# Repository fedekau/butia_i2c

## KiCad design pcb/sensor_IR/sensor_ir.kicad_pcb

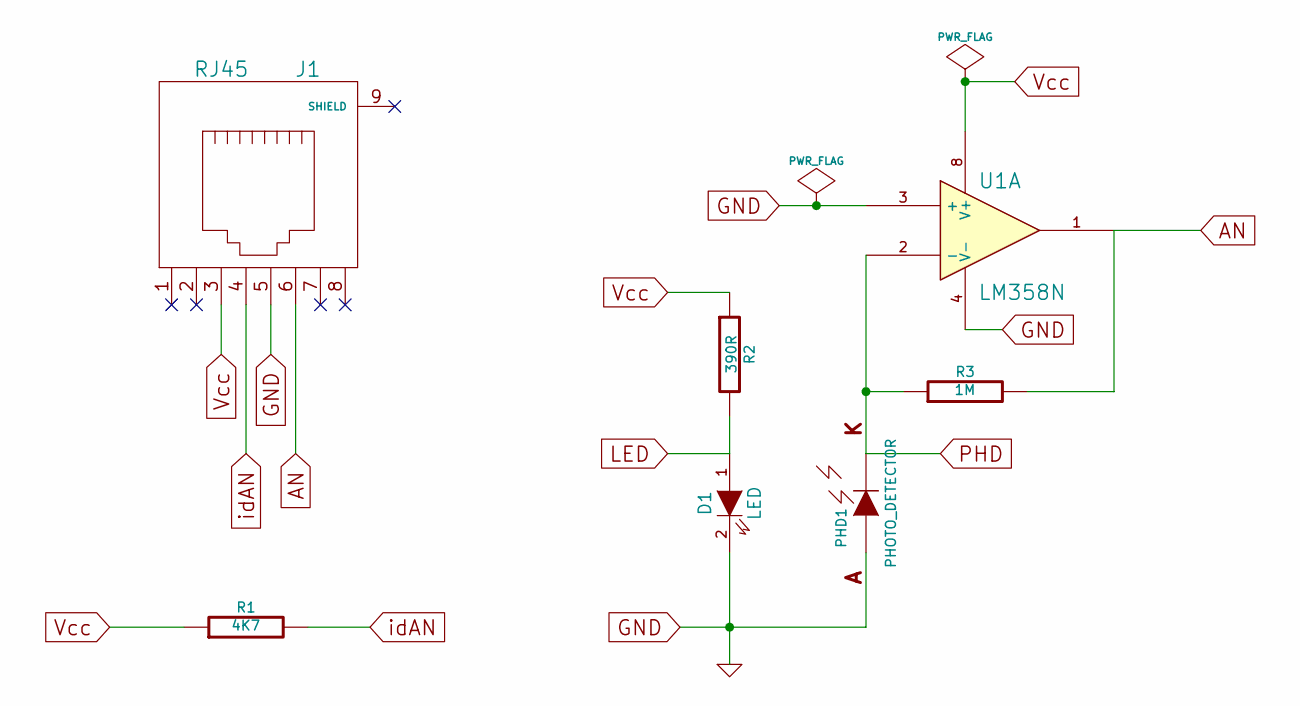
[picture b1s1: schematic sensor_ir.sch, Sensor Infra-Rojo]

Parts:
D1: LED
J1: RJ45
PHD1: PHOTO_DETECTOR
R1: 4K7
R2: 390R
R3: 1M
U1: LM358N

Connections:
AN: J1.6, R3.2, U1.1
GND: D1.2 (K), J1.5, PHD1.1 (A), U1.3 (+), U1.4 (V-)
LED: D1.1 (A), R2.2
PHD: PHD1.2 (K), R3.1, U1.2 (-)
Vcc: J1.3, R1.1, R2.1, U1.8 (V+)
idAN: J1.4, R1.2

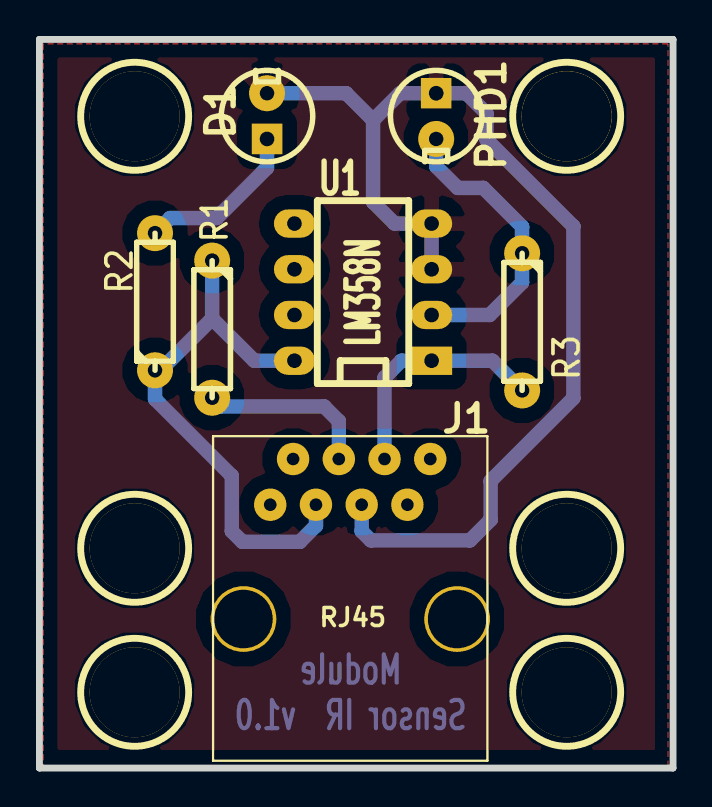
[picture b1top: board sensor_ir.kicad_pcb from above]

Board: 2 copper layers, 35.2 x 40.5 mm, 7 parts (0 on the bottom side), 6 nets.

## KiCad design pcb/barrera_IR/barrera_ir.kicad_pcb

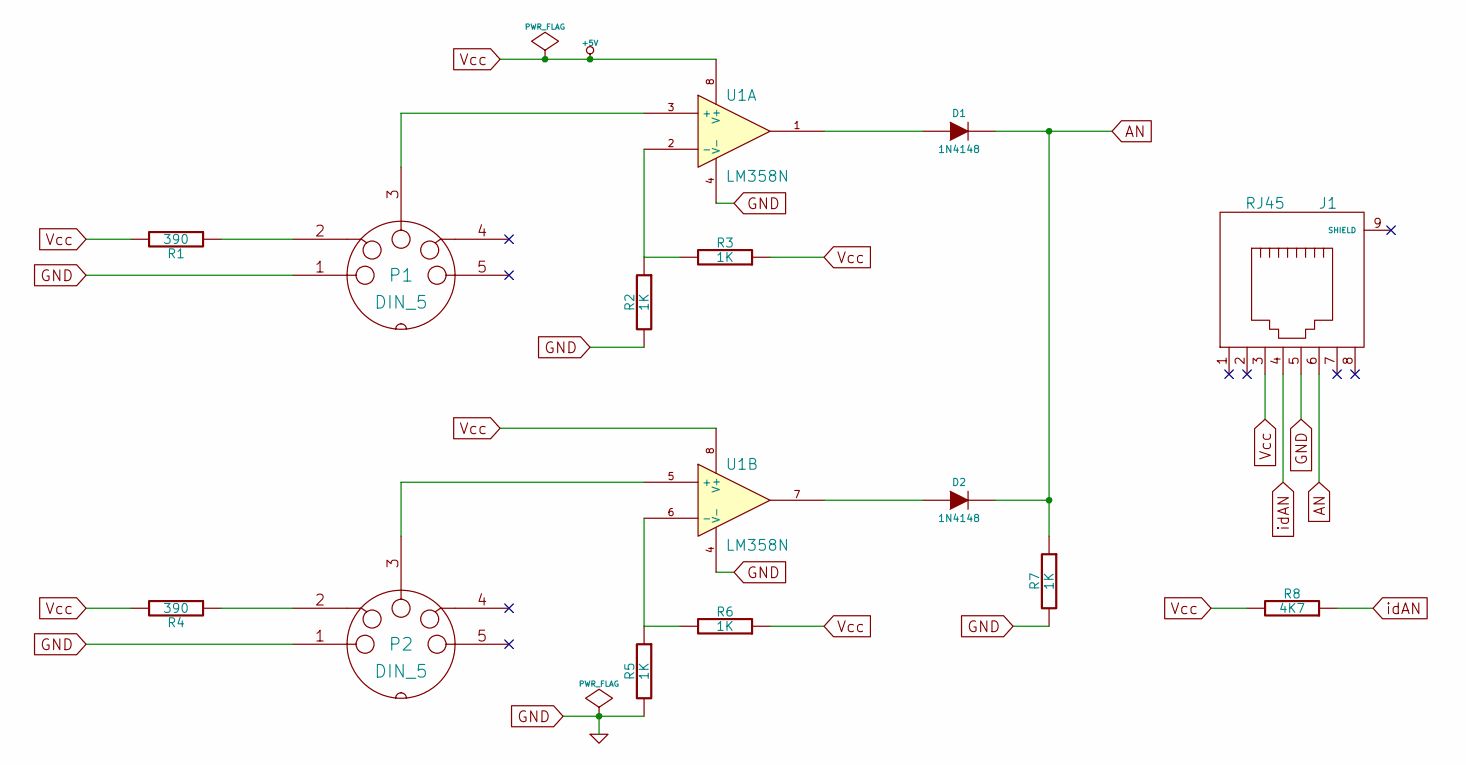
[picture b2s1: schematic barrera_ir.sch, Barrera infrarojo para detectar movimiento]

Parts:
D1, D2: 1N4148
J1: RJ45
P1, P2: DIN_5
R1, R4: 390
R2, R3, R5, R6, R7: 1K
R8: 4K7
U1: LM358N

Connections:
AN: D1.2 (K), D2.2 (K), J1.6, R7.1
GND: J1.5, P1.1, P2.1, R2.2, R5.2, R7.2, U1.4 (V-)
unnamed: D2.1 (A), U1.7
unnamed: R5.1, R6.2, U1.6 (-)
unnamed: P2.2, R4.1
unnamed: D1.1 (A), U1.1
unnamed: R2.1, R3.2, U1.2 (-)
unnamed: P1.2, R1.1
unnamed: P1.3, U1.3 (+)
unnamed: P2.3, U1.5 (+)
Vcc: J1.3, R1.2, R3.1, R4.2, R6.1, R8.2, U1.8 (V+)
idAN: J1.4, R8.1

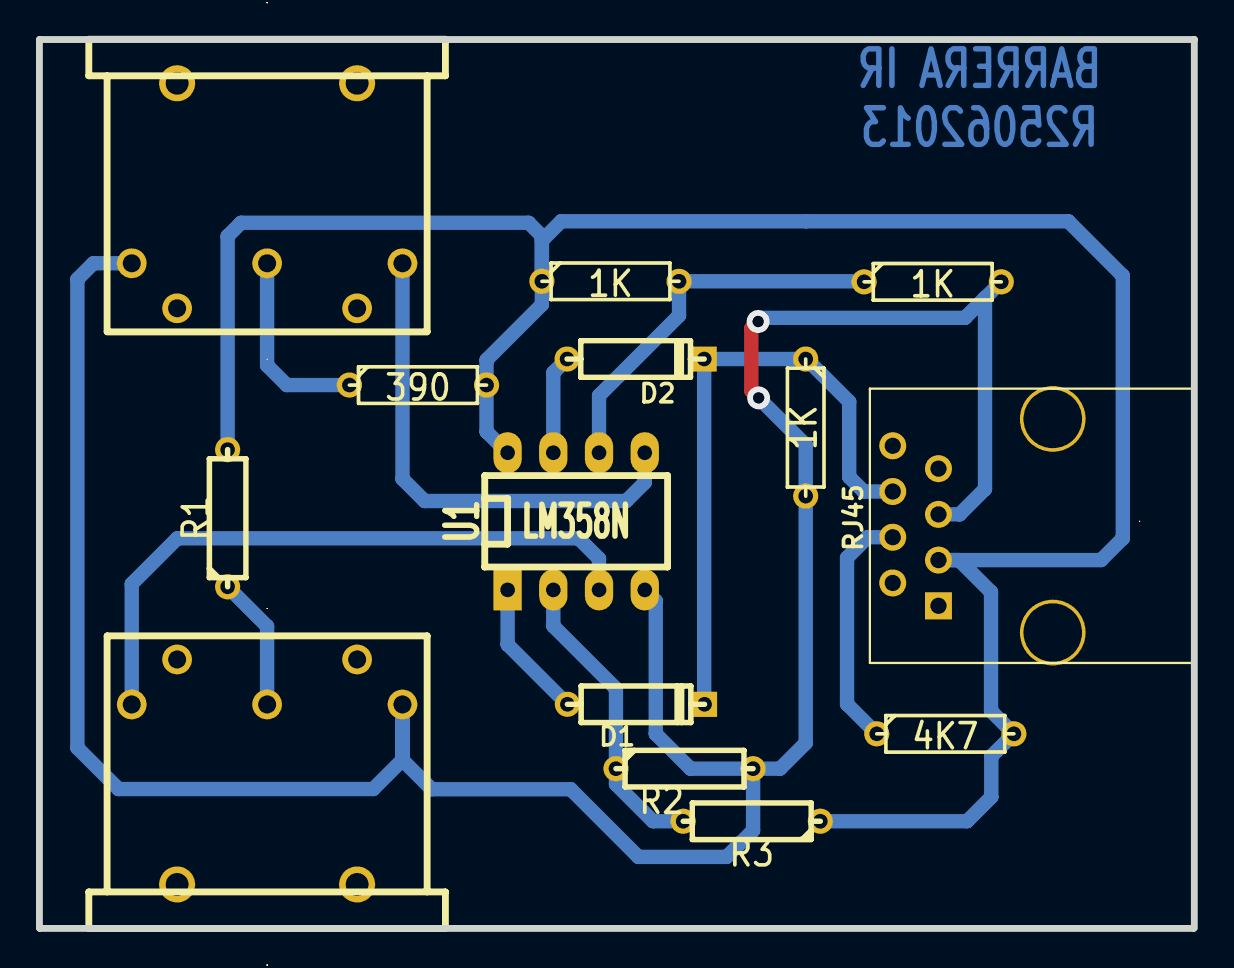
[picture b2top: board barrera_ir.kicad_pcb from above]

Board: 2 copper layers, 64.2 x 49.4 mm, 14 parts (0 on the bottom side), 12 nets.

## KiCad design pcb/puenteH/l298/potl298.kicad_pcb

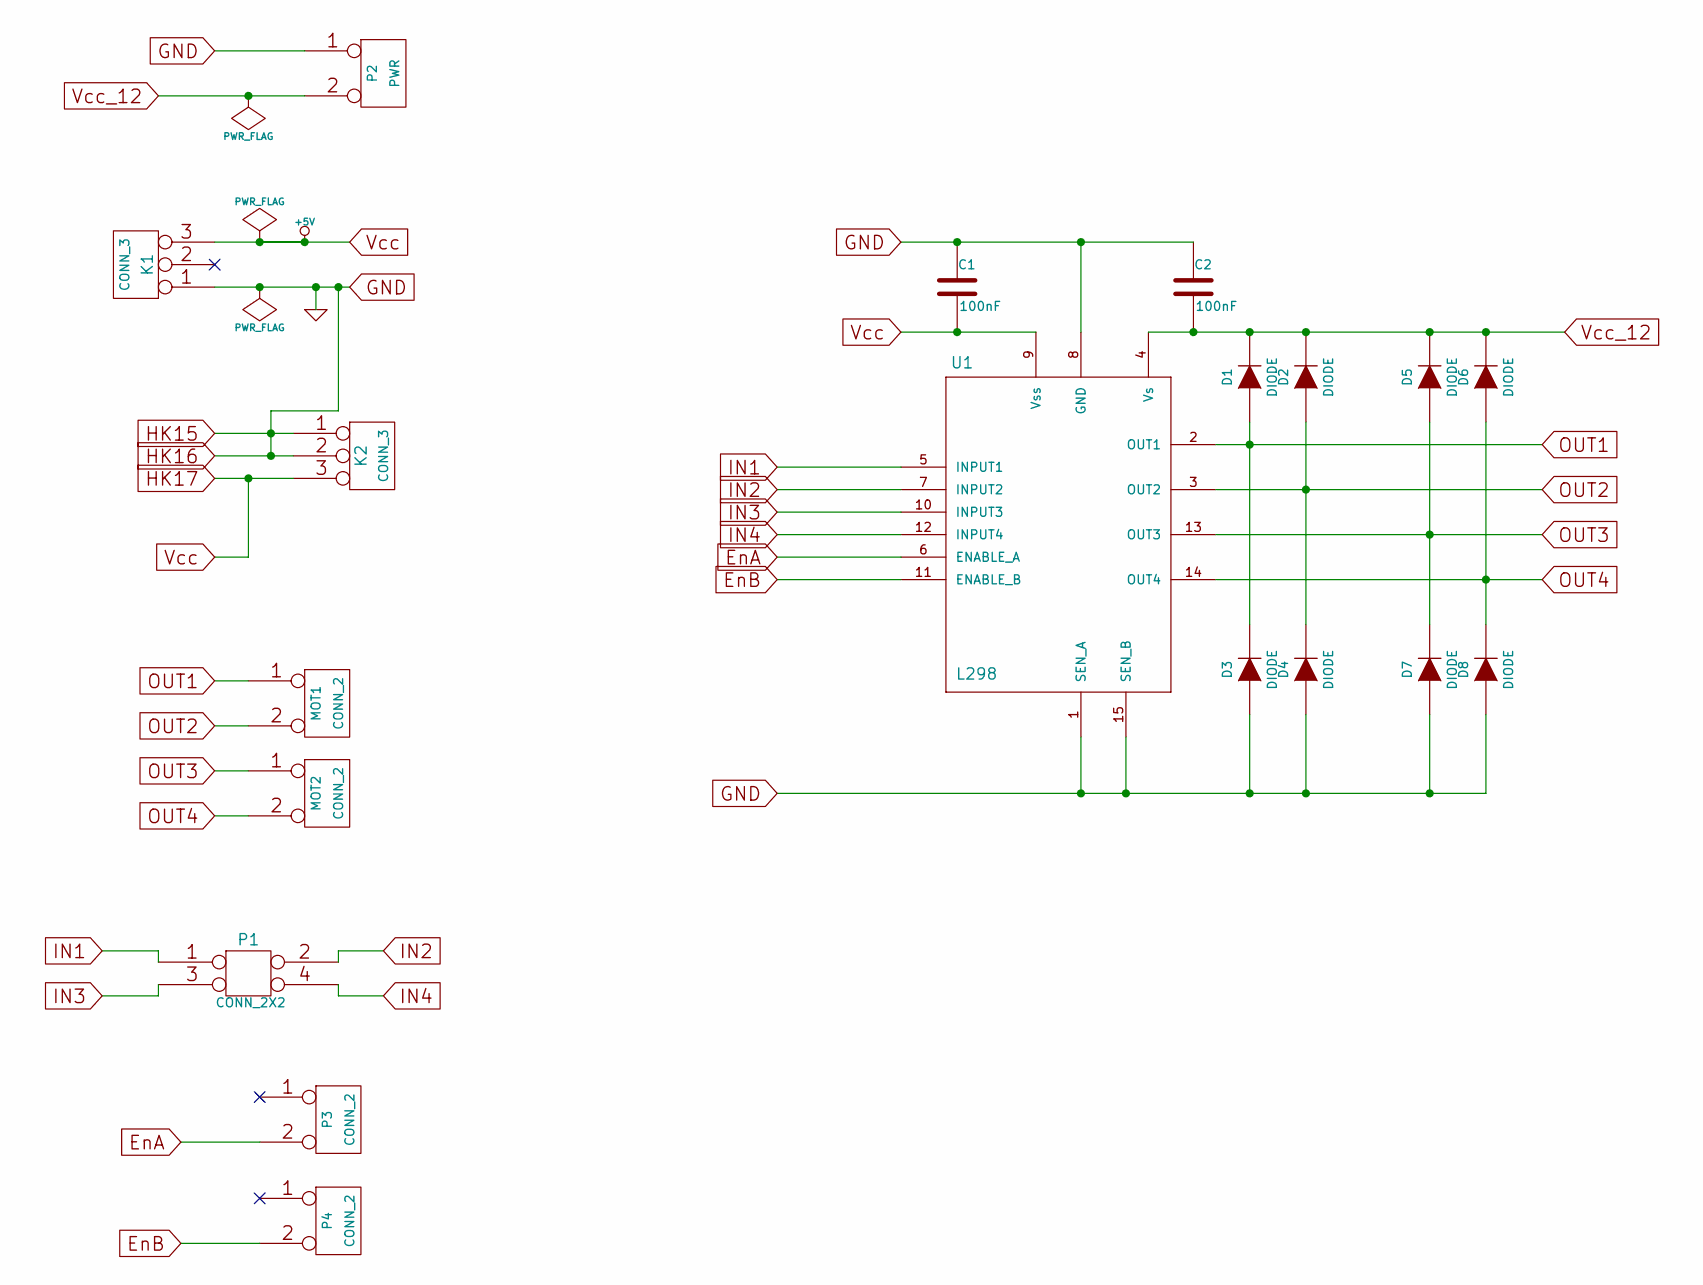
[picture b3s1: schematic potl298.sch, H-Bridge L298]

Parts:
C1, C2: 100nF
D1, D2, D3, D4, D5, D6, D7, D8: DIODE
K1, K2: CONN_3
MOT1, MOT2: CONN_2
P1: CONN_2X2
P2: PWR
P3, P4: CONN_2
U1: L298; drivers_motor

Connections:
EnA: P3.2 (PM), U1.6 (ENABLE_A)
EnB: P4.2 (PM), U1.11 (ENABLE_B)
GND: C1.1, C2.1, D3.1 (A), D4.1 (A), D7.1 (A), D8.1 (A), K1.1, K2.1, K2.2 (PM), P2.1, U1.1 (SEN_A), U1.8 (GND), U1.15 (SEN_B)
HK17: C1.2, K1.3, K2.3, U1.9 (Vss)
IN1: P1.1, U1.5 (INPUT1)
IN2: P1.2, U1.7 (INPUT2)
IN3: P1.3, U1.10 (INPUT3)
IN4: P1.4, U1.12 (INPUT4)
OUT1: D1.1 (A), D3.2 (K), MOT1.1, U1.2 (OUT1)
OUT2: D2.1 (A), D4.2 (K), MOT1.2 (PM), U1.3 (OUT2)
OUT3: D5.1 (A), D7.2 (K), MOT2.1, U1.13 (OUT3)
OUT4: D6.1 (A), D8.2 (K), MOT2.2 (PM), U1.14 (OUT4)
Vcc_12: C2.2, D1.2 (K), D2.2 (K), D5.2 (K), D6.2 (K), P2.2 (PM), U1.4 (Vs)

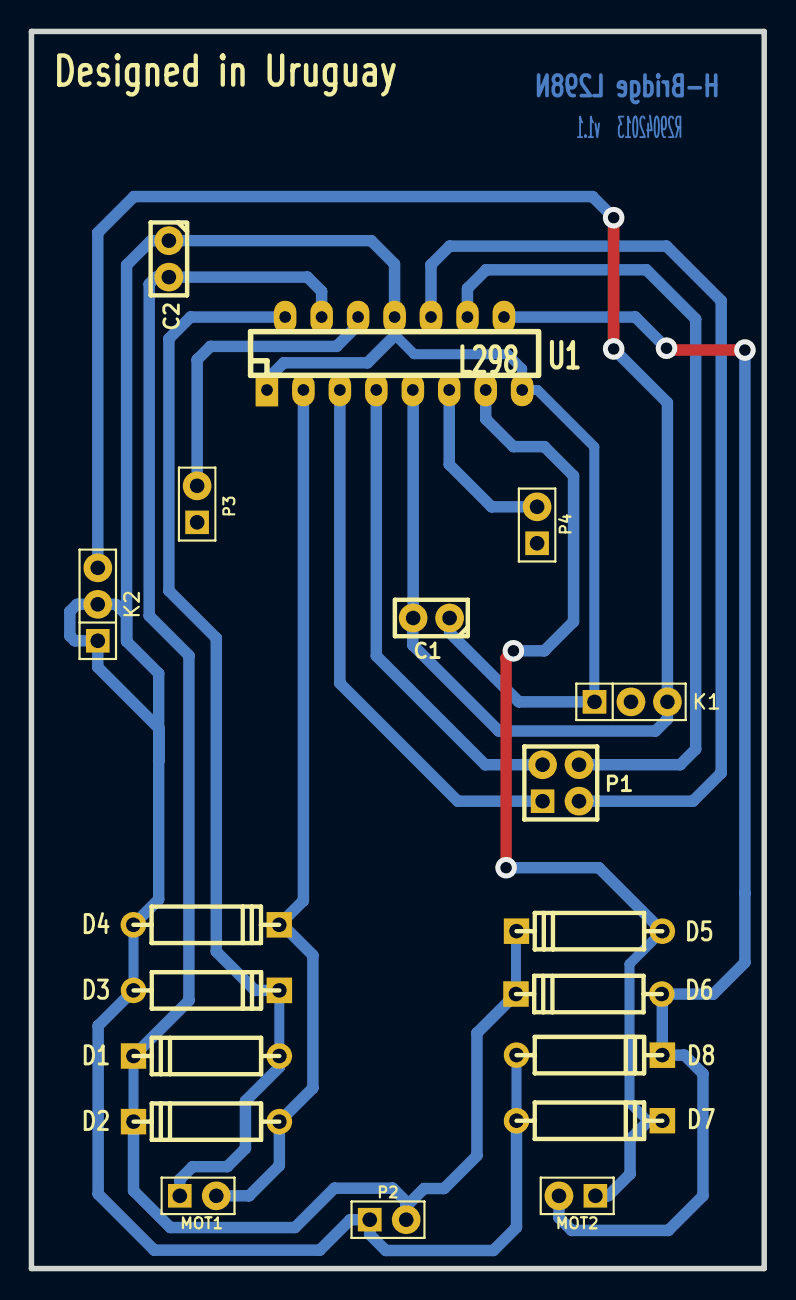
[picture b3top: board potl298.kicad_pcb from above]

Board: 2 copper layers, 51.1 x 86.2 mm, 19 parts (0 on the bottom side), 13 nets.

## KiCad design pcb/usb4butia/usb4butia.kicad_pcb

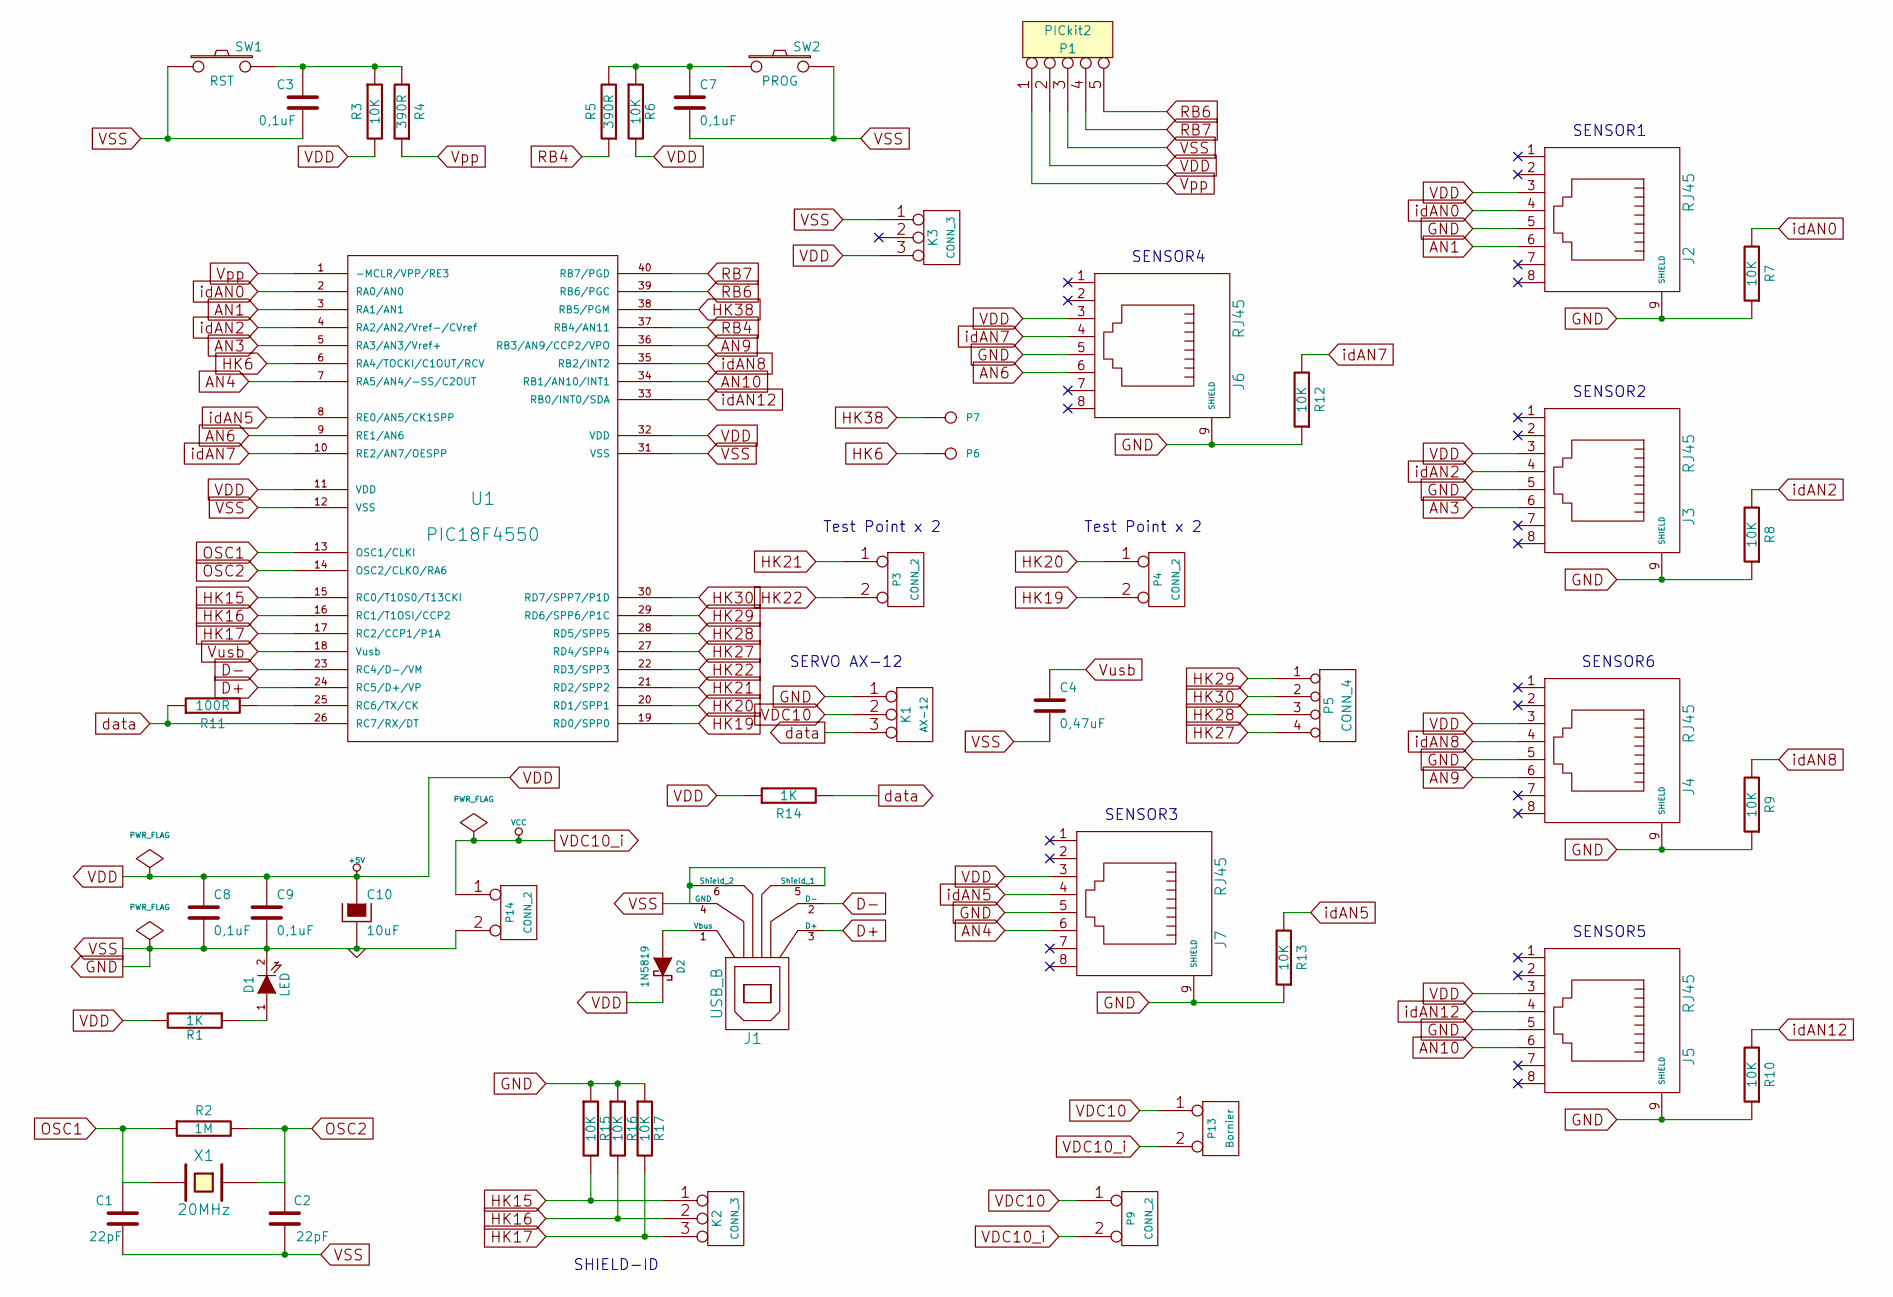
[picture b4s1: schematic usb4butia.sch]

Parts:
C1, C2: 22pF
C3, C7, C8, C9: 0,1uF
C4: 0,47uF
C10: 10uF
D1: LED
D2: 1N5819
J1: USB_B
J2, J3, J4, J5, J6, J7: RJ45
K1: AX-12
K2, K3: CONN_3
P1: PICkit2
P3, P4, P9, P14: CONN_2
P5: CONN_4
P6, P7: CONN_1
P13: Bornier
R1, R14: 1K
R2: 1M
R3, R6, R7, R8, R9, R10, R12, R13, R15, R16, R17: 10K
R4, R5: 390R
R11: 100R
SW1: RST
SW2: PROG
U1: PIC18F4550
X1: 20MHz

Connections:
AN1: J2.6, U1.3 (RA1/AN1)
AN3: J3.6, U1.5 (RA3/AN3/Vref+)
AN4: J7.6, U1.7 (RA5/AN4/-SS/C2OUT)
AN6: J6.6, U1.9 (RE1/AN6)
AN9: J4.6, U1.36 (RB3/AN9/CCP2/VPO)
AN10: J5.6, U1.34 (RB1/AN10/INT1)
D+: J1.3 (D+), U1.24 (RC5/D+/VP)
D-: J1.2 (D-), U1.23 (RC4/D-/VM)
GND: C1.2, C2.2, C3.2, C4.2, C7.2, C8.2, C9.2, C10.2, D1.2 (K), J1.4 (GND), J1.5 (Shield_1), J1.6 (Shield_2), J2.5, J2.9 (SHIELD), J3.5, J3.9 (SHIELD), J4.5, J4.9 (SHIELD), J5.5, J5.9 (SHIELD), J6.5, J6.9 (SHIELD), J7.5, J7.9 (SHIELD), K1.1, K3.1, P1.3, P14.2 (PM), R7.1, R8.1, R9.1, R10.1, R12.1, R13.1, R15.1, R16.1, R17.1, SW1.1, SW2.2, U1.12 (VSS), U1.31 (VSS)
HK6: P6.1, U1.6 (RA4/TOCKI/C1OUT/RCV)
HK15: K2.1, R15.2, U1.15 (RC0/T10S0/T13CKI)
HK16: K2.2 (PM), R16.2, U1.16 (RC1/T1OSI/CCP2)
HK17: K2.3, R17.2, U1.17 (RC2/CCP1/P1A)
HK19: P4.2 (PM), U1.19 (RD0/SPP0)
HK20: P4.1, U1.20 (RD1/SPP1)
HK21: P3.1, U1.21 (RD2/SPP2)
HK22: P3.2 (PM), U1.22 (RD3/SPP3)
HK27: P5.4, U1.27 (RD4/SPP4)
HK28: P5.3, U1.28 (RD5/SPP5)
HK29: P5.1, U1.29 (RD6/SPP6/P1C)
HK30: P5.2, U1.30 (RD7/SPP7/P1D)
HK38: P7.1, U1.38 (RB5/PGM)
unnamed: C7.1, R5.2, R6.1, SW2.1
unnamed: C3.1, R3.1, R4.2, SW1.2
unnamed: D1.1 (A), R1.1
unnamed: D2.1 (A), J1.1 (Vbus)
unnamed: R11.2, U1.25 (RC6/TX/CK)
OSC1: C1.1, R2.1, U1.13 (OSC1/CLKI), X1.2
OSC2: C2.1, R2.2, U1.14 (OSC2/CLKO/RA6), X1.1
RB4: R5.1, U1.37 (RB4/AN11)
RB6: P1.5, U1.39 (RB6/PGC)
RB7: P1.4, U1.40 (RB7/PGD)
VDC10: K1.2 (PM), P9.1, P13.1
VDC10_i: P9.2 (PM), P13.2 (PM), P14.1
VDD: C8.1, C9.1, C10.1, D2.2 (K), J2.3, J3.3, J4.3, J5.3, J6.3, J7.3, K3.3, P1.2, R1.2, R3.2, R6.2, R14.1, U1.11 (VDD), U1.32 (VDD)
Vpp: P1.1, R4.1, U1.1 (-MCLR/VPP/RE3)
Vusb: C4.1, U1.18 (Vusb)
data: K1.3, R11.1, R14.2, U1.26 (RC7/RX/DT)
idAN0: J2.4, R7.2, U1.2 (RA0/AN0)
idAN2: J3.4, R8.2, U1.4 (RA2/AN2/Vref-/CVref)
idAN5: J7.4, R13.2, U1.8 (RE0/AN5/CK1SPP)
idAN7: J6.4, R12.2, U1.10 (RE2/AN7/OESPP)
idAN8: J4.4, R9.2, U1.35 (RB2/INT2)
idAN12: J5.4, R10.2, U1.33 (RB0/INT0/SDA)

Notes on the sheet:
SENSOR6
Test Point x 2
SENSOR5
SENSOR4
SENSOR3
SENSOR2
SENSOR1
SERVO AX-12
SHIELD-ID

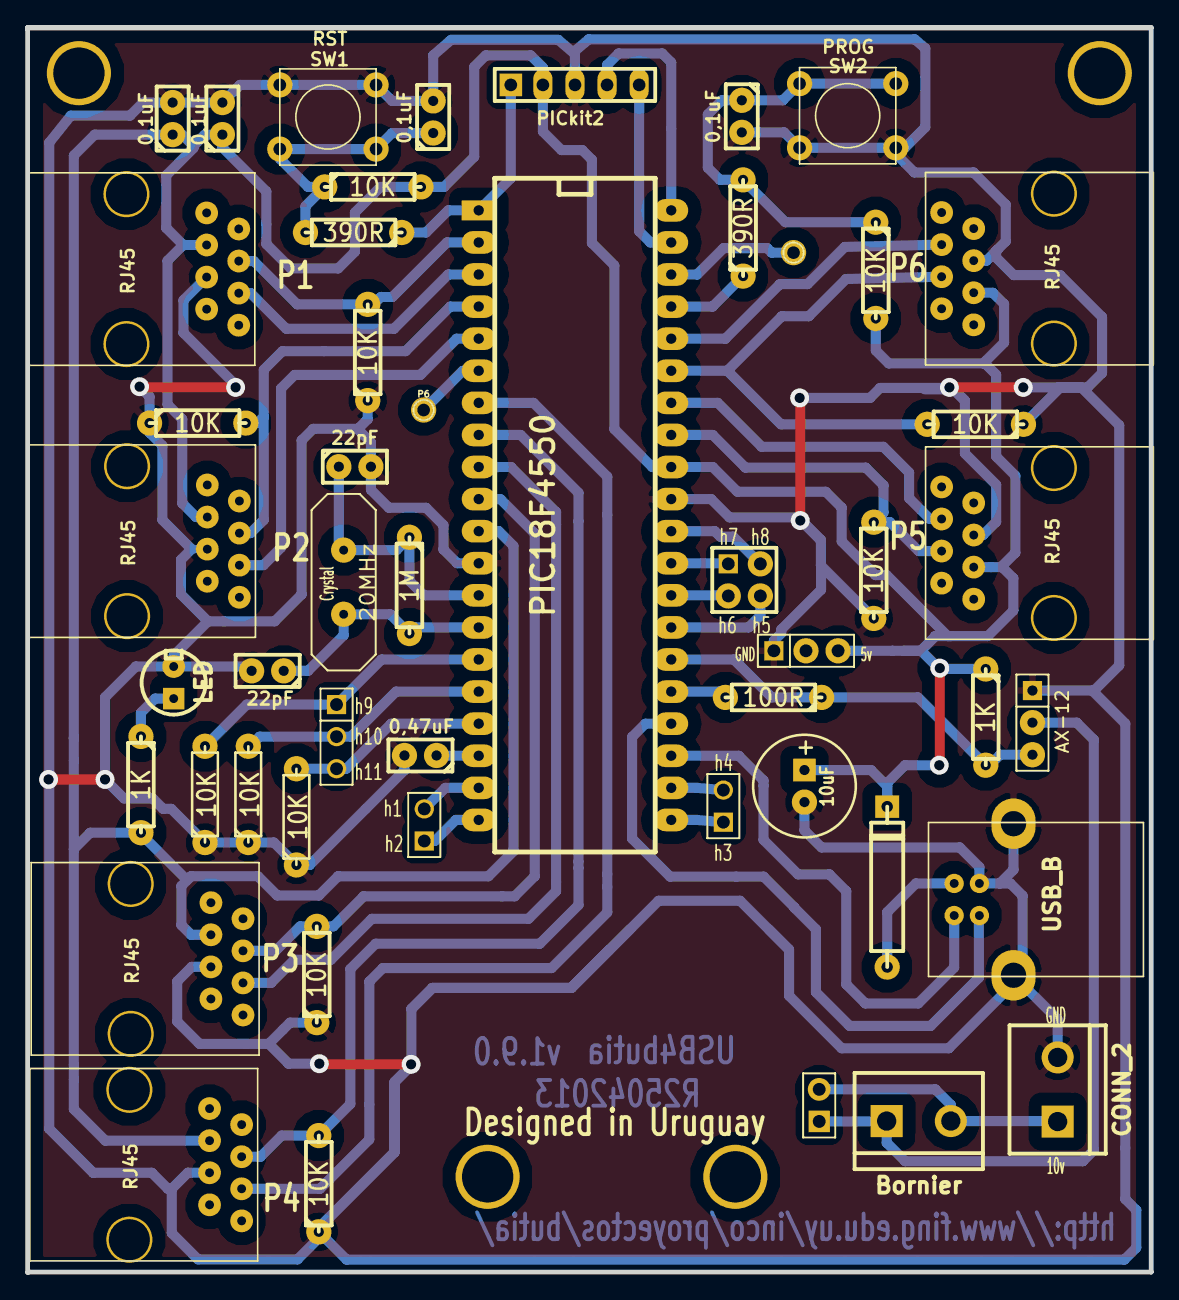
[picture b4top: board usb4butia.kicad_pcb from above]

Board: 2 copper layers, 88.9 x 98.5 mm, 50 parts (0 on the bottom side), 44 nets.

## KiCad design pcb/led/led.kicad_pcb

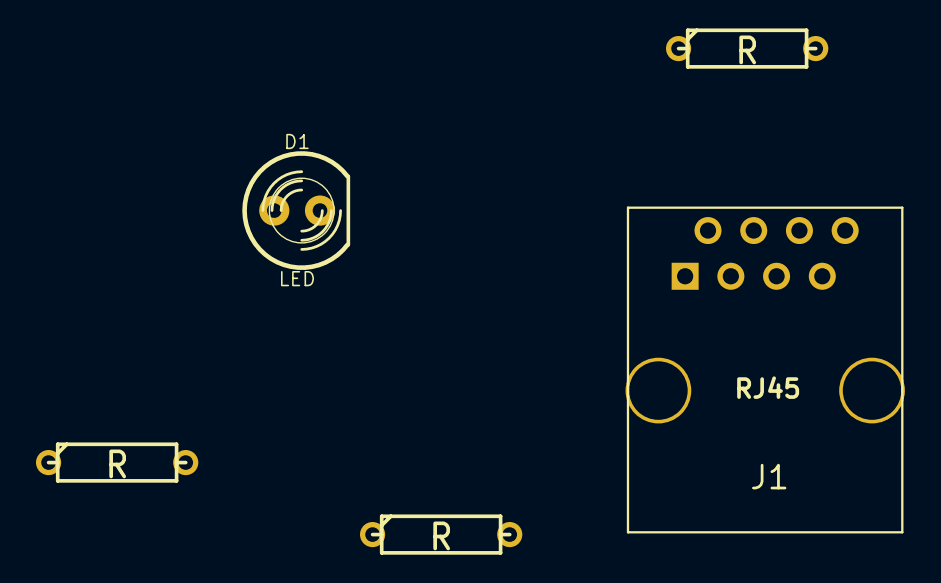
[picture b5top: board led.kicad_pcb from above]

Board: 2 copper layers, 5 parts (0 on the bottom side), 4 nets, no tracks yet.

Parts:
D1: LED; LED-5MM
J1: RJ45; RJ45_8
R1, R2, R3: R; R3

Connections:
AN: J1.6, R1.1
unnamed: D1.2, R3.1
VDD: D1.1, J1.3, R2.2
idAN: J1.4, R2.1

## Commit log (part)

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2012-03-28 Fixed somes compling errors
2012-04-12 BoarPortDescriptor was defined
2012-04-12 Added usb4butia module and deleted some Constants from adminModule
2012-04-13 changes in usb4butia module and definitions in handlerManager module.
2012-04-13 Implementation for Analogic reading Detection pin, usb4butia.c was created
2012-04-16 Add sensorType definition, sensorTable and function initSensorTable
2012-04-16 IN hotplug&play fixed get_device_type, now send the correct parameter to this function
2012-04-16 Add coments author
2012-04-17 closePnP implemented
2012-04-17 Add PnP archive, start implement tabe with resistance values
2012-04-17 Take out some cosntants definitions
2012-04-18 Replace old table for table_device_id_resistance_value, and add xlm for proyect
2012-04-18 Reimplement get_device_type
2012-04-19 added autogenerated files to .gitignore
2012-04-19 Repare gets functions
2012-04-19 Function for read analog sessor in ports
2012-04-19 Fix some compling error... is not compling yet
2012-04-19 Fixed more compiling erros, now is compiling
2012-04-20 Still fixing error, still compile
2012-04-20 Fix ldr location
2012-04-21 Change dicrection and add pull up for AX12 conector, v1.6
2012-04-21 added new modules definitions
2012-04-21 deleted re-definited functions definitions
2012-04-21 Implemented getPortDescriptor and deleted some unused functions
2012-04-21 changed prototype of received functions
2012-04-21 Function ports are pointer to functions
2012-04-21 changes to the loopback module to support mplabX
2012-04-21 adding DefaultEndpoint
2012-04-24 added led user module.
2012-04-25 Test resistance it's working need somes adjusts
2012-04-25 Add ADCON1 and ADCON2 configurations
2012-04-25 Reimplemeted getDeviceType function and are real resistance value in table
2012-04-25 Added PCBs for usb4butia and sensors
2012-05-01 still testing read...
2012-05-04 seems to be reading ok from the serial port
2012-05-05 Some changes...
2012-05-05 Fixed compiling error, now is compiling
2012-05-07 Change order into register hotplug fuction
2012-05-07 fix openpnp
2012-05-07 more consise return ERROR
2012-05-07 added more proyect objects
2012-05-07 firts working pnp
2012-05-08 added proyect objects
2012-05-08 add gpìo module
2012-05-08 intermediate commit
2012-05-09 added to gitignore makefile's
2012-05-09 proyect configuration, reorganization
2012-05-10 changed getDigitalData
2012-05-10 fixed digital read
2012-05-10 changed all getDigitalData
2012-05-22 sharp sensor with GND cape
2012-05-23 Delet pull up from sharp sensor, shapr v1.7
2012-05-23 Rename somes islets in ldr pcb
2012-05-23 six ports working ok
2012-05-24 Add .lib in ldr sensor
2012-05-24 more file in gitignore
2012-05-24 Fix error in net file of sharp sensor
2012-05-24 Change design sharp, v1.8
2012-05-28 translating to English
2012-05-28 change read version
2012-05-28 removed old files
2012-05-28 change imports to new files
2012-05-31 Add Bridge as componets
2012-06-05 USB4butia v1.7.1
2012-06-05 USB5butia 1.7.2
2012-06-07 Formalizate Bridges definition usb4butia1.7.3
2012-06-07 usb4butia1.7.4
2012-06-08 Still working in usb4buti 1.7.4
2012-06-08 usb4butia1.7.5 prototipe completed
2012-06-14 changes in motores.c
2012-06-18 some sunday's cleanup ;) nothing important
2012-06-20 Add PCB_Edges cape in LDR
2012-06-20 Add PCB_Edges cape sharp
2012-06-20 Add silkscreen usb4butia1.8.1
2012-06-20 Change name in PCB to Module Button
2012-06-21 working on auto-detection
2012-06-21 added autoDetectWheels function
2012-06-21 first version of autodetection wheels working
2012-06-21 Reduce the large of the pcb usb4butia1.8.2
2012-06-22 Move holder islet usb4butia1.8.4
2012-06-25 changed timeout in readSerial function
2012-06-25 default all pins to analogic. Enable analogic at the beggining
2012-06-25 changes in read_ver_butia to keep back compatibility
2012-06-26 renamed distance module to keep compatibility
2012-06-26 Added Fabricado por Eneka module sharp
2012-06-26 Added Fabricado por Eneka module LDR
2012-06-26 Fix text spell in module botton
2012-07-02 cleanup
2012-07-08 adding changes for flashing without pressing the programming button in git butia to git usb4all
2012-07-08 fixed first_port_read bug :)
2012-07-09 aded fsusb autogenerated to .gitignore
2012-07-09 GET_HANDLER_SIZE command returns getMaxHandler() in order to speed up the interaction between the bobot and the USB4butia. Also some sundays cleanup made.
2012-07-09 added changes from butia/fua
2012-07-10 change uTab to const uTab
2012-07-10 removing some warnings
2012-07-11 slow down plug and play frecuency as alan requested a fast detection. Tested and worked ok.
2012-07-13 version 22
2012-07-14 fixed first_time_read_port bug with ax12 motors disconected. seems to be problem of concurrency
2012-07-14 this is a biiig problem! fixed..
2012-07-19 added light sensor module
2012-07-19 added files to project
2012-07-24 removed what I suppose is debug code
2012-08-15 fixed bug when making an int from 2 bytes. High byte was nulled :(
2012-08-22 adding original author credits
2012-08-22 added usb skeleton
2012-08-23 kernel_module: more merging
2012-09-11 creat new folder for usb4all
2012-09-11 restruct folders
2012-09-12 get volt
2012-09-13 increas sharp and ldr islets size
2012-09-17 Increase pads size USB4butia v1.8.5
2012-10-12 added skeleton user module
2012-10-12 added generic user module to read voltage
2012-10-12 added user module to read resistance values
2012-10-25 Arreglos en vías para que no se produzcan errores al correr un DRC.
2012-10-30 Change the bridge components for vias
2012-11-06 Change names of files and add new component jack audio
2012-11-06 Add new component jack audio in schematic and pcb
2012-11-07 redifined max_devices constant. Added configurations since added new modules to project
2012-11-07 trying new autodetection funtion for motors
2012-11-07 added 22k resistence
2012-11-08 Add border line and finish v1.0
2012-11-13 Edit size pads and change some tracks
2012-11-14 added hackpoints module to control pin27 to 30 -no autodetection merged
2012-11-14 deleted warning in config prototype function from modules
2012-11-14 deleting prototype definitions and pointers warnings
2012-11-15 Add connector for pins RD0 & RD1. Add jumper for power supply motors
2012-11-20 Add new layer and edit pad drill
2012-11-21 Add module led
2012-11-22 changes to hackpoints to deal with IN mode
2012-11-23 Add butia's logo in front layer
2012-11-28 resize of linker sections
2012-11-28 some cleanup
2012-11-29 renamed hackp to user module
2012-11-29 changes to user modules. del configuration function
2012-11-29 changes to rm configuration function from modules
2012-11-29 changes to linker sections
2012-12-04 finished hackpoints-testing
2012-12-07 Add holes for hold
2012-12-14 Add pins for interface between the H bridge and the uC
2012-12-18 Add table of true
2012-12-21 Cocumentation hackpoints
2012-12-21 Complete table of true
2012-12-26 Relay module
2013-01-16 Add voltage PCB desing and modified PCB resistance desing
2013-01-25 fixed loopback user module
2013-01-30 fixing silk
2013-01-30 template for sensors
2013-02-06 loopback must return opcode as all functions
2013-02-06 change final style of tab in usr modules
2013-02-06 hackp have one function SET_MODE and one WRITE
2013-02-06 add configurations changes
2013-02-13 increment version to diferenciate changes with previous firmware
2013-02-22 add new mplab project for bootloader
2013-02-28 added new user module to write & read info with ax
2013-03-05 More silk fixing
2013-03-06 add Desinged in Uruguay and fix a bug
2013-03-06 working in copper logo
2013-03-07 fix silk things
2013-03-07 Fix more silk errors and add gerber version
2013-03-07 usb4butia1.8.8 release without logo
2013-03-14 added shield cc module
2013-03-14 included module shield into project
2013-03-14 test t1s through mod
2013-03-18 defined new res to cc motor
2013-03-21 Fix problem islet in LDR, add led develop module
2013-04-04 Add pull ups for pins 15, 16 & 17
2013-04-05 Driver for DC motors with L298
2013-04-08 new configuration -basic one
2013-04-08 rm re-definition of byte and old imports
2013-04-08 config file
2013-04-10 user module to specific msgs to ax12-working on it
2013-04-11 working only with necessary functions
2013-04-11 some modifications to work in new ax12library
2013-04-13 H bridge L298 completed for connect to usb4butia (version 1.8.9 and futures)
2013-04-15 identation and coments
2013-04-15 added sensors to project to test all functionalities
2013-04-16 fix utab two warnings
2013-04-23 fix autodetection for ax12
2013-04-23 ax getVersion returns 3 bytes as all modules
2013-04-24 Jorge changes
2013-04-25 fix a lot of types
2013-04-25 rm redefinition
2013-04-25 no tris changed in each function
2013-04-25 admin & butia versions updated
2013-04-26 Changing pull ups for pull downs in pins 15, 16 and 17
2013-04-26 adding already open check in admin
2013-04-26 if open then return handler
2013-04-27 add handlerFromTableEntry definition in header file
2013-04-29 changing pull down for pull up
2013-05-02 increase drill holders size
2013-05-02 fix and form update
2013-05-02 Fix silk in ldr module
2013-05-03 new module led and somes changes
2013-05-04 fix uTab missing declaration
2013-05-04 motors direction to byte
2013-05-08 minor message corrections
2013-05-16 getVolt of butia module returns a byte
2013-05-16 add configurations
2013-05-22 First version of infra red barrier
2013-05-22 use 001 for shield cc
2013-05-23 correction bug in circuit of infra red barrier
2013-05-30 H bridge with IC L298HN
2013-06-10 fix value resistence
2013-06-10 add version 1.9.0 gerbers of usb4butia
2013-06-20 Add gerber v1.1 for shield motors
2013-06-25 Change the wired AND for wired OR in the output of barrier IR
2013-06-28 un-hardcoded pnp handler
2013-06-28 missing cast
2013-07-02 pull down pin Hk 15 and 16 in vertical shield
2013-07-23 fix led user module
2013-07-23 add led user module
2013-07-24 a lot of changes
2013-07-24 change ch9 define
2013-07-28 correct lenght of bytes
2013-07-28 fix pnp getVersion function
2013-07-30 Sensor IR for measure distance
2013-07-31 compact usr_motors - add CC initial move
2013-07-31 minor changes
2013-08-01 fix loopBack to new style
2013-08-01 equal endpoint types like in usbdefs_std
2013-08-01 remove unused T0Proxy module from project
2013-08-01 add the rest of generic modules
2013-08-01 more elegant motors calls
2013-08-05 remove hack of ever set as output the pins in CC
2013-08-05 generic PCB sensor
2013-08-06 add Temp module
2013-08-07 hacking for space problem
2013-08-07 correct handler name
2013-08-07 remove dynamicPolling (not used at moment)
2013-08-07 remove processIO functions
2013-08-07 fix sense of cc motor function
2013-08-18 fix cast to motors type to byte
2013-08-18 compact pnp port init
2013-08-18 more tabs fixed
2013-08-19 update user module skeleton
2013-08-20 add old message function in admin - some tabs fixes
2013-08-26 only use on endpoint (bulk)
2013-08-26 use EPIN_IS_BUSY instead mUSBGenTxIsBusy
2013-08-26 comment unused functions
2013-08-26 remove unused variables
2013-08-26 remove more unused variables
2013-09-04 more spaces for user_sec
2013-09-04 add generic sensor and actuators
2013-10-03 fix number of endpoints
2013-11-09 fixing the memory check error - skip first 64bytes
2013-11-10 correct place for usb4all shields
2013-11-10 add name of modifier
2013-11-12 init getVolt variable at start
2014-02-12 adding support for CC motors set vel
2014-03-19 Change firmware version
2014-05-06 fix error with direction
2014-05-09 fix admin version
2014-05-29 fixed copy paste error x
2014-05-30 pnp table to code sys mem section
2014-08-05 fix speed motors
2014-09-01 fix sens
2014-09-25 changing the firmware version
2014-12-03 Fix problem with sense AX12
2015-06-04 add buzzer and relay - remove led and temp
2015-07-13 testing for firmware 13 rele
2015-08-26 add eeprom user module
2015-08-26 some clean of eeprom module
2016-11-18 blink y 3 segundos
2016-11-18 250ms sin blink
2016-11-22 Ejecuta read desde pc
2016-11-25 Add user module for i2c
2016-11-25 Rename i2c file
